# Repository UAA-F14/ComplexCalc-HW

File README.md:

# ComplexCalc — Hardware Version 🔌⚡

**A standalone embedded calculator for complex n×n linear systems (Ax=b)** — no PC required at runtime. Custom STM32F411 PCB with a 16-button keypad and an ILI9341 TFT display, built for electronics students and AC circuit analysis.

> [!NOTE]
> **Work in progress.** Firmware is functional (keypad input, TFT UI, Gauss-Jordan solver); the PCB is still being routed (some ADC connections are pending — see [Design](#-design-pcb)).

---

## 📁 Repository Structure

```
├── code/
│   └── 06ComplexCalcDasProject/   # STM32CubeIDE / CMake firmware project
│       ├── Core/
│       │   ├── Inc/               # ComplexGJ.h (solver), TFT_Screen.h, display_ui.h, ...
│       │   └── Src/                # SWComplexGJ.c (solver), TFT_Screen.c, display_ui.c, main.c, ...
│       └── Drivers/                # Vendored STM32 HAL + CMSIS (ST-generated, not project code)
├── design/
│   └── ComplexCalc/                # KiCad schematic + PCB (in progress)
└── README.md
```

The actual project logic lives in `Core/Inc` / `Core/Src`; everything under `Drivers/` is STM32CubeMX-generated boilerplate.

---

## 🎯 Overview

- **MCU:** STM32F411C(C/E)U (Cortex-M4, UFQFPN48) — the same chip used on "BlackPill" dev boards, but here on a custom PCB, you can use the minimum sistem or insert a blackpill in the socket, it works either way.
- **Display:** ILI9341 TFT over SPI.
- **Input:** 16-button matrix keypad (4×4), wired directly on the PCB.
- **Power:** coin-cell battery holder + AMS1117-3.3 LDO regulator.
- **Solver:** Gauss-Jordan elimination, single-precision (`float`) complex arithmetic, systems from 2×2 up to 4×4.

No serial terminal, USB host, or PC connection is needed to use the calculator — power it on, and the keypad + screen are the whole interface. (USB/SWD is only used to flash firmware.)

---

## 🚀 Build & Flash

**Using STM32CubeIDE (recommended):**
1. Open STM32CubeIDE.
2. File → Open Projects from File System.
3. Select `code/06ComplexCalcDasProject/`.
4. Build (`Ctrl+B`), then flash over USB/SWD (`Ctrl+Alt+X`).

**Using CMake + the ARM GCC toolchain (also supported by this project):**
```bash
cd code/06ComplexCalcDasProject
cmake --preset Debug      # or: Release
cmake --build --build-preset Debug
```
This uses the project's own `cmake/gcc-arm-none-eabi.cmake` toolchain file — you'll need `arm-none-eabi-gcc` and `ninja` installed.

---

## 🎮 Usage

On power-up, the screen prompts for the system size (`2`–`4`). From there:

| Input | Action |
|---|---|
| `0`–`9` | Enter digits (toggles between real/imaginary part) |
| `=` | Confirm entry / advance |
| `S` + `P` (combo) | Cycle display theme |

Once the full A matrix and b vector are entered, the solver runs on-device and the result is shown on screen — no PC needed.

---

## 🧮 Solver Details

- **Algorithm:** Gauss-Jordan elimination (`solve_complex_system` in `ComplexGJ.h`/`SWComplexGJ.c`).
- **Precision:** single-precision float, `EPSILON = 1e-7` for singularity checks.
- **Maximum size:** 4×4 (`N_MAX`), matching the keypad-driven size range (2–4).
- **Error handling:** returns `SOLVER_ERR_INVALID_SIZE` / `SOLVER_ERR_SINGULAR` for out-of-range sizes or singular matrices.

---

## 🖥️ Design (PCB)

KiCad project at `design/ComplexCalc/` — schematic + PCB for the keypad, MCU, TFT header, and power circuitry.

*Routing in progress — some ADC-related connections are still pending. A rendered board image will replace this screenshot once the layout is finished.*

A datasheet-vs-schematic power supply review (VCAP sizing, VBAT, NRST, HSE crystal value) is available at [`docs/ComplexCalc-HW_power_supply_review_en.pdf`](docs/ComplexCalc-HW_power_supply_review_en.pdf) ([Spanish version](docs/ComplexCalc-HW_power_supply_review.pdf)).

---

## 🤝 Contributing

1. Firmware changes go in `code/06ComplexCalcDasProject/Core/`.
2. PCB changes go in `design/ComplexCalc/` (KiCad 8+).
3. Open a PR against this repo.

## 📞 Issues

Report bugs or hardware questions via this repo's [Issues](https://github.com/UAA-F14/ComplexCalc-HW/issues).

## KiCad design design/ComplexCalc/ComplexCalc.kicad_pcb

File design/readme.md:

# Design

## Collaborators

- **das** — base layout and initial design.
- **robertoloro** — routing the rest of the board.
- **IKGB** — checking and validating the minimum system.

# Logfile
## 8-28

Pending to connect multiple veins of minimum system.

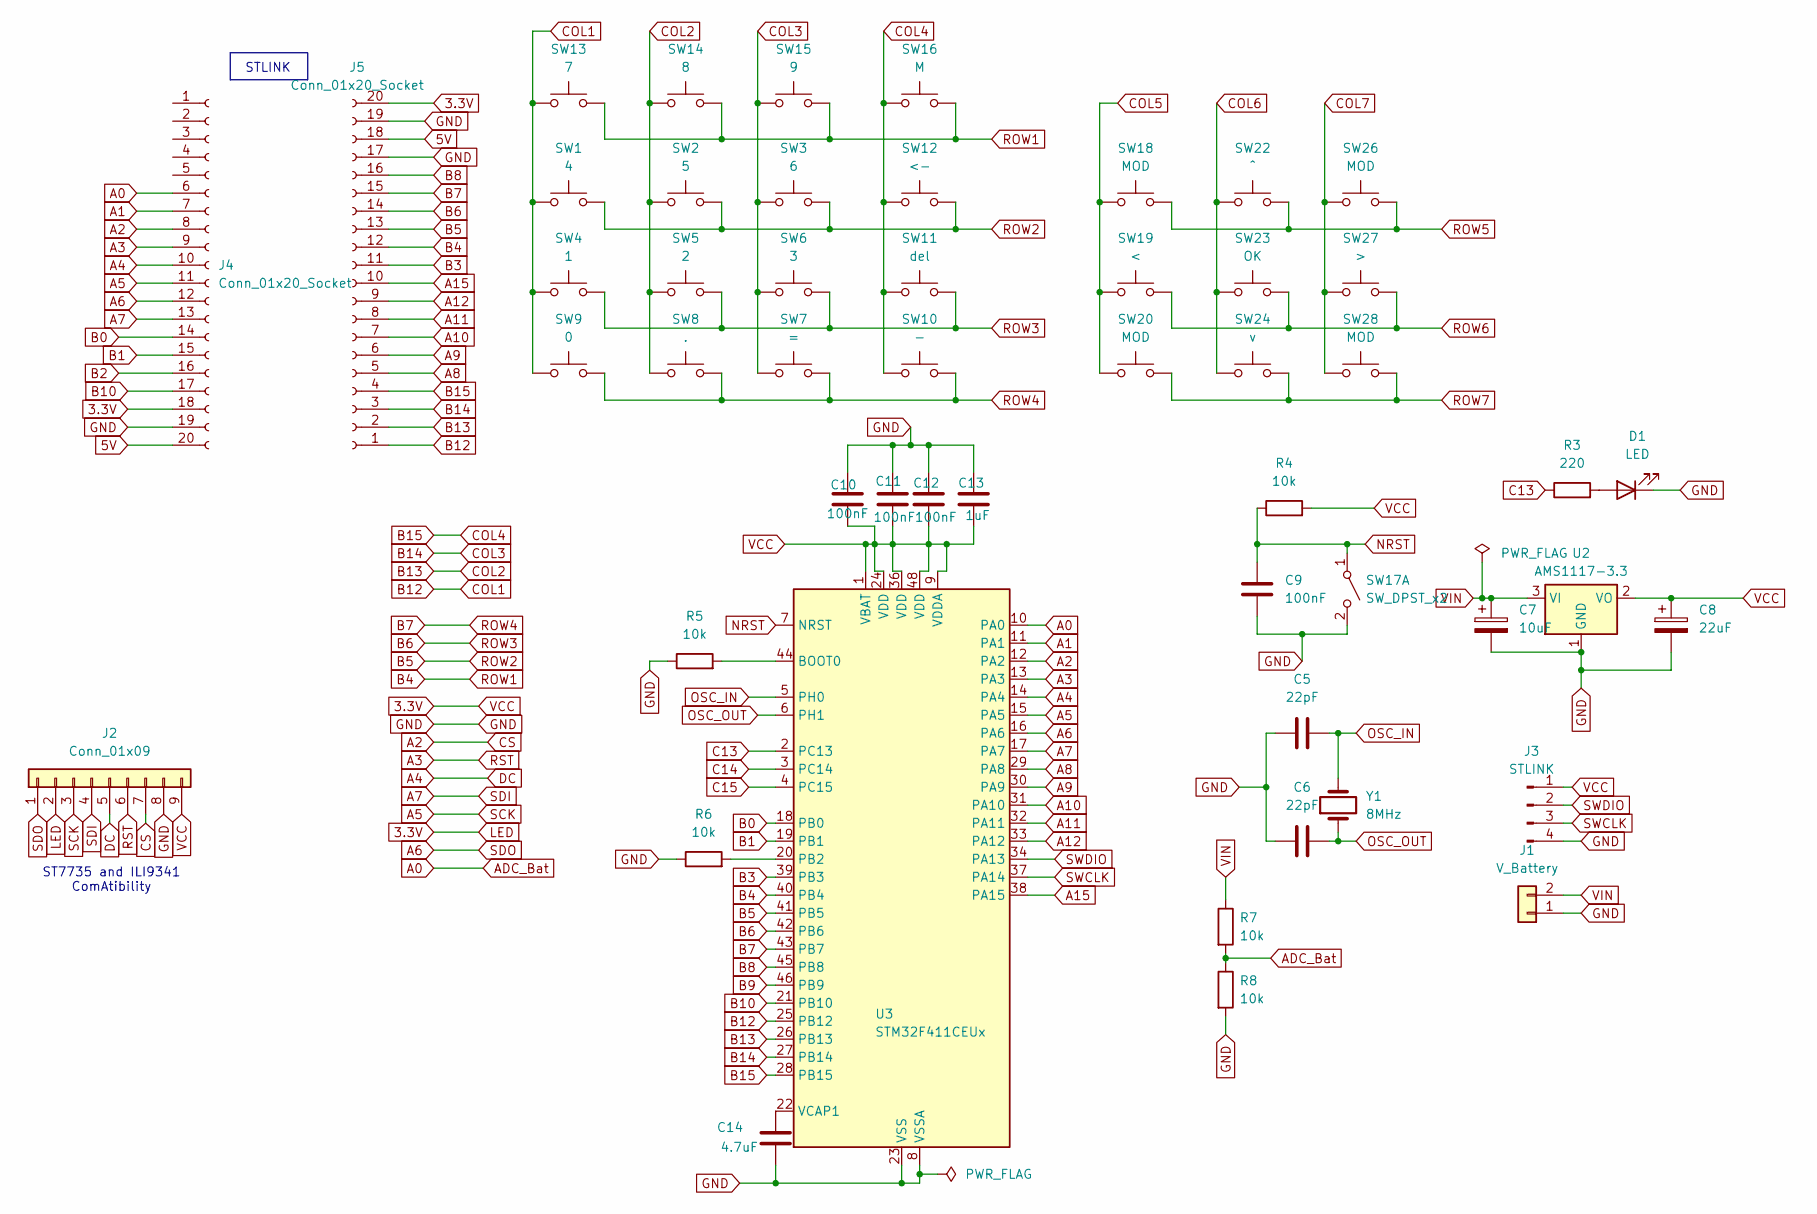
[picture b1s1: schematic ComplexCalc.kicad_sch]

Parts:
C5, C6: 22pF; C_0805_2012Metric_Pad1.18x1.45mm_HandSolder
C7: 10uF; C_0805_2012Metric_Pad1.18x1.45mm_HandSolder
C8: 22uF; C_0805_2012Metric_Pad1.18x1.45mm_HandSolder
C9, C10, C11, C12: 100nF; C_0805_2012Metric_Pad1.18x1.45mm_HandSolder
C13: 1uF; C_0805_2012Metric
C14: 4.7uF; C_0805_2012Metric_Pad1.18x1.45mm_HandSolder
D1: LED; LED_0603_1608Metric
J1: V_Battery; PinHeader_1x02_P2.54mm_Vertical
J2: Conn_01x09; CR2013-MI2120
J3: STLINK; PinHeader_1x04_P2.54mm_Vertical
J4, J5: Conn_01x20_Socket; PinHeader_1x20_P2.54mm_Vertical
R3: 220; R_0805_2012Metric
R4, R5, R6, R7, R8: 10k; R_0805_2012Metric
SW1: 4; SW_PUSH-12mm
SW2: 5; SW_PUSH-12mm
SW3: 6; SW_PUSH-12mm
SW4: 1; SW_PUSH-12mm
SW5: 2; SW_PUSH-12mm
SW6: 3; SW_PUSH-12mm
SW7: =; SW_PUSH-12mm
SW8: .; SW_PUSH-12mm
SW9: 0; SW_PUSH-12mm
SW10: -; SW_PUSH-12mm
SW11: del; SW_PUSH-12mm
SW12: <-; SW_PUSH-12mm
SW13: 7; SW_PUSH-12mm
SW14: 8; SW_PUSH-12mm
SW15: 9; SW_PUSH-12mm
SW16: M; SW_PUSH-12mm
SW17: SW_DPST_x2; Untitled
SW18, SW20, SW26, SW28: MOD; SW_PUSH-12mm
SW19: <; SW_PUSH-12mm
SW22: ^; SW_PUSH-12mm
SW23: OK; SW_PUSH-12mm
SW24: v; SW_PUSH-12mm
SW27: >; SW_PUSH-12mm
U2: AMS1117-3.3; SOT-223-3_TabPin2
U3: STM32F411CEUx; QFN-48-1EP_7x7mm_P0.5mm_EP5.6x5.6mm
Y1: 8MHz; Crystal_SMD_EuroQuartz_MQ2-2Pin_7.0x5.0mm

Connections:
3.3V: C8.1, C10.1, C11.1, C12.1, C13.1, J2.2, J2.9, J3.1, J4.18, J5.20, R4.2, U2.2 (VO), U3.1 (VBAT), U3.9 (VDDA), U3.24 (VDD), U3.36 (VDD), U3.48 (VDD)
5V: J4.20, J5.18
A0: J4.6, R7.2, R8.1, U3.10 (PA0)
A1: J4.7, U3.11 (PA1)
A2: J2.7, J4.8, U3.12 (PA2)
A3: J2.6, J4.9, U3.13 (PA3)
A4: J2.5, J4.10, U3.14 (PA4)
A5: J2.3, J4.11, U3.15 (PA5)
A6: J2.1, J4.12, U3.16 (PA6)
A7: J2.4, J4.13, U3.17 (PA7)
A8: J5.5, U3.29 (PA8)
A9: J5.6, U3.30 (PA9)
A10: J5.7, U3.31 (PA10)
A11: J5.8, U3.32 (PA11)
A12: J5.9, U3.33 (PA12)
A15: J5.10, U3.38 (PA15)
B0: J4.14, U3.18 (PB0)
B1: J4.15, U3.19 (PB1)
B2: J4.16
B3: J5.11, U3.39 (PB3)
B4: J5.12, SW13.2, SW14.2, SW15.2, SW16.2, U3.40 (PB4)
B5: J5.13, SW1.2, SW2.2, SW3.2, SW12.2, U3.41 (PB5)
B6: J5.14, SW4.2, SW5.2, SW6.2, SW11.2, U3.42 (PB6)
B7: J5.15, SW7.2, SW8.2, SW9.2, SW10.2, U3.43 (PB7)
B8: J5.16, U3.45 (PB8)
B9: U3.46 (PB9)
B10: J4.17, U3.21 (PB10)
B12: J5.1, SW1.1, SW4.1, SW9.1, SW13.1, U3.25 (PB12)
B13: J5.2, SW2.1, SW5.1, SW8.1, SW14.1, U3.26 (PB13)
B14: J5.3, SW3.1, SW6.1, SW7.1, SW15.1, U3.27 (PB14)
B15: J5.4, SW10.1, SW11.1, SW12.1, SW16.1, U3.28 (PB15)
C13: R3.1, U3.2 (PC13)
C14: U3.3 (PC14)
C15: U3.4 (PC15)
COL5: SW18.1, SW19.1, SW20.1
COL6: SW22.1, SW23.1, SW24.1
COL7: SW26.1, SW27.1, SW28.1
GND: C5.2, C6.2, C7.2, C8.2, C9.1, C10.2, C11.2, C12.2, C13.2, C14.2, D1.1 (K), J1.1, J2.8, J3.4, J4.19, J5.17, J5.19, R5.1, R6.1, R8.2, SW17.2 (B), U2.1 (GND), U3.8 (VSSA), U3.23 (VSS), U3.35 (VSS), U3.47 (VSS), U3.49 (VSS)
NRST: C9.2, R4.1, SW17.1 (A), U3.7 (NRST)
unnamed: D1.2 (A), R3.2
unnamed: R5.2, U3.44 (BOOT0)
unnamed: R6.2, U3.20 (PB2)
unnamed: C14.1, U3.22 (VCAP1)
OSC_IN: C5.1, U3.5 (PH0), Y1.2
OSC_OUT: C6.1, U3.6 (PH1), Y1.1
ROW5: SW18.2, SW22.2, SW26.2
ROW6: SW19.2, SW23.2, SW27.2
ROW7: SW20.2, SW24.2, SW28.2
SWCLK: J3.3, U3.37 (PA14)
SWDIO: J3.2, U3.34 (PA13)
VIN: C7.1, J1.2, R7.1, U2.3 (VI)

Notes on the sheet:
STLINK
ST7735 and ILI9341 ComAtibility

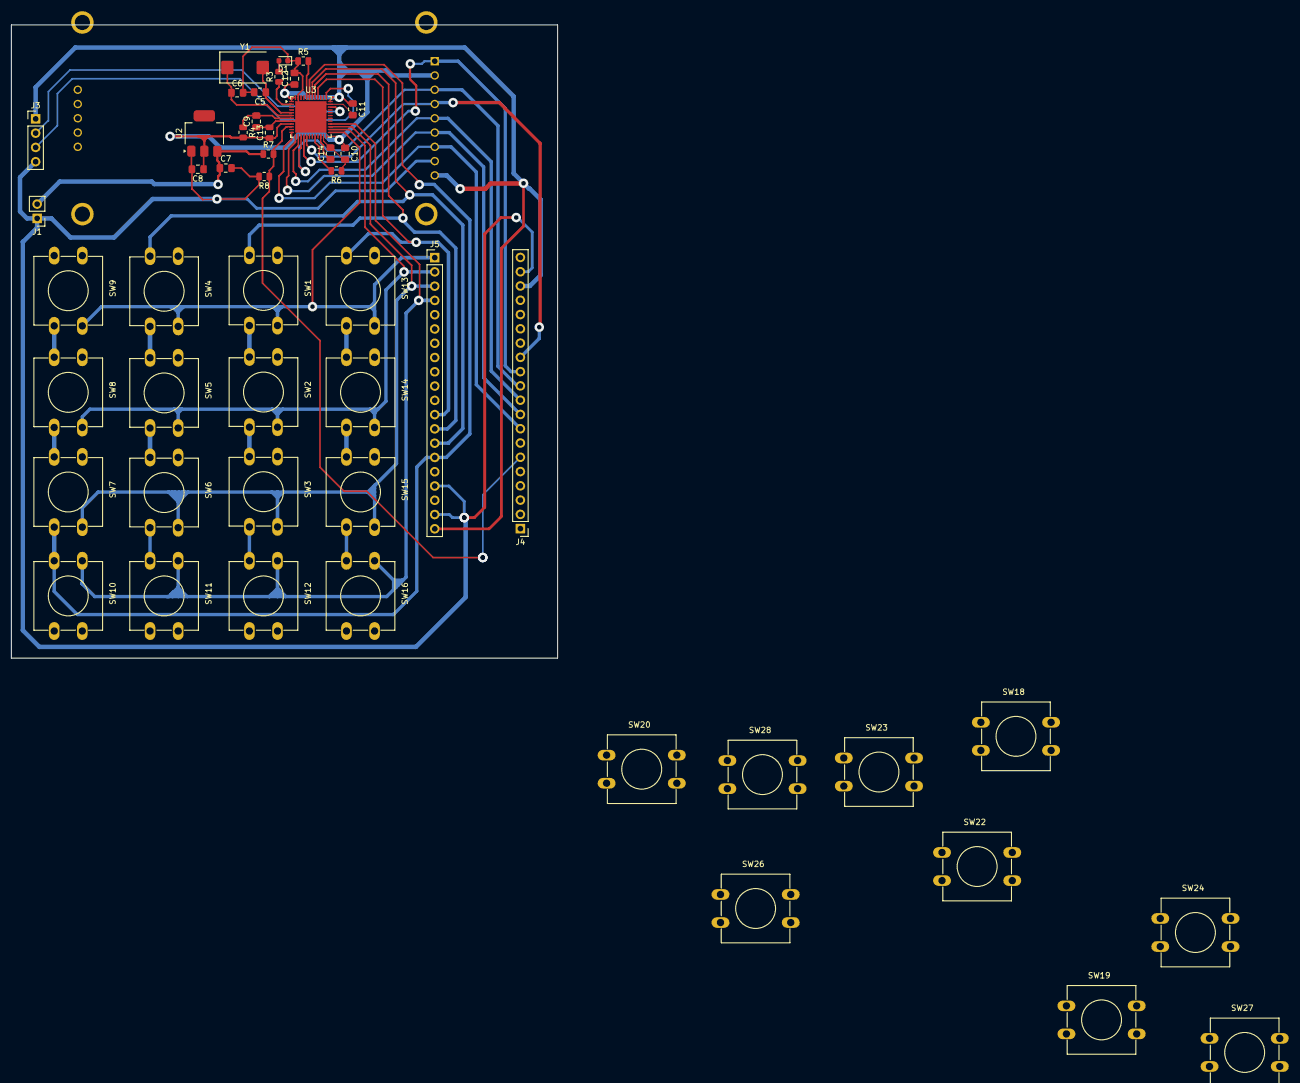
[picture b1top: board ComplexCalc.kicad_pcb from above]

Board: 2 copper layers, 97.2 x 112.7 mm, 50 parts (1 on the bottom side), 47 nets.
